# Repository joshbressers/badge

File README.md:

This code is no longer maintained, everything got too complicated. You should go to the new home of this project
https://github.com/OpenBadgeProject

# Open Badge Project

This is the Open Badge Project. The idea behind this is to have a very low cost, low power electronic badge. These could be built just for fun, or if you're throwing a conference, feel free to use the PCB as the badge, maybe build some, maybe let the folks at the conference build them.

Electronic badges have gotten pretty hip, but they seem to suffer from two primary problems.
1) They are very expensive
1) They need a lot of batteries

The goal of the Open Badge Project was to build a badge that costs $5 or less and can run for a day or more on one 2032 battery.

The badge as it stands right now will only cost $5 if you build A LOT (1000 or more). The cost is closer to $6 or $7 for smaller batches at the moment, but that's still pretty reasonable.

### Types
There are two versions of the badge. One is a through hole badge that's very easy to solder. It was designed with human fabricators in mind. The kicad files in the main branch are for the through hole model.

There is also a surface mount version in the [surface-mount](https://github.com/joshbressers/badge/tree/surface-mount) branch. This version of the badge can be sent off to a fabricator to be mass produced.

Both badge versions use the same code.

## How does it work?
The badge itself runs on a microprocessor called an ATTINY85. It has 8K of program space, 512 bytes (yes, bytes) of memory. That microprocessor then drives 3 shift registers. One for the button input, and two for the display output. Shift registers shouldn't be used to drive LEDs, but it works, and doing it this way keeps the cost down.

The PCB can be shipped off to one of the countless PCB manufacturers that exist. There is room on the front for a logo. There is also plenty of room on the back for graphics. Instructions for swapping in your own logo can be found below.

The PCB was designed using KiCad, version 7.0 to be precise. Your mileage may very if you try to use other versions.

## Parts List
You can generate a bill of materials from KiCad, but for the sake of simplicity here is a list of all the parts.

- 1 [ATTINY85](https://www.digikey.com/en/products/detail/microchip-technology/ATTINY85-20PU/735469)
- 1 PCB (you have to get this made, you can't buy them)
- 2 [CD74HC595E](https://www.digikey.com/en/products/detail/texas-instruments/CD74HC595E/1507396) shift registers
- 1 [CD4021BE](https://www.digikey.com/en/products/detail/texas-instruments/CD4021BE/67261) shift register
- 1 [2032 battery holder](https://www.digikey.com/en/products/detail/adam-tech/BH-25C-1/13537703)
- 8 [100 Ohm resistors](https://www.digikey.com/en/products/detail/stackpole-electronics-inc/CF14JT100R/1741261)
- 8 [100K Ohm resistors](https://www.digikey.com/en/products/detail/stackpole-electronics-inc/CF14JT10K0/1741265)
- 6 [Buttons](https://www.amazon.com/gp/product/B07VSNN9S2/ref=ppx_yo_dt_b_asin_title_o00_s00?ie=UTF8&th=1)
- 1 [8x8 LED Display](https://www.aliexpress.us/item/3256805713726832.html?spm=a2g0o.order_list.order_list_main.11.64611802KkD7xH&gatewayAdapt=glo2usa)

There may be better places to purchase these things than these links. Please submit a PR if you find something better.

## How to change the logo
KiCad has a tool called "Image Converter". This application lets you turn an image into a footprint that can be added to the PCB layout.

When you run the tool, there is a button on the left called "Load Source Image". If you have a black and white image to start with that's the best. You can use any image but things get weird.

Once you load an image you will need to watch the size. The "Output Size" field is what matters here. It will take a few tries to get it right. There's about 3 inches by 1.7 inches of space to work with on the front.

Use the "Front Solder Mask" layer. Make sure you use Footprint for the output layer.

Click Export to file. Save the file in the badge-footprints.pretty directory.

Now open the "PCB Editor" application. Make sure the "F. Silkscreen" layer is selected on the right.

You will have to click on and delete the existing logo. Now from the menu Place -> Add Footprint

If you search for "badge" in the text box you should see your logo show up in the list. Double click it, then place it where it fits. If the logo isn't sized right, go back to the Image Converter and try again.

## How to order PCBs
If you want to have PCBs made, you need to export the Gerber files from the PCB Editor. The Gerber files are what you send the PCB manufacturer.

Run the PCB Editor, then File -> Fabrication Outputs -> Gerbers

Create a new directory to hold the files (there will be more than one). For example let's call it badge_gerber. Leave the default settings alone, it should do the right thing.

Then click Plot. Then click "Generate Drill Files" and "Generate Drill File" on the window that pops up. Your directory now has the files need to create the PCB in it.

The PCB manufacturer will want that directory turned into a zip file and uploaded. You're on your own to figure that part out.

## How to program the chip

In order to program the ATTINY85 you will need a programmer. There is a lovely page that explains how to use an arduino as your [programmer](https://www.instructables.com/How-to-Program-an-Attiny85-From-an-Arduino-Uno/)

The reset pin on this chip is special. We are purposely not using that pin (so we really only have 5 IO pins now) because if you use the reset pin, you now require a high voltage programmer. Since we want people to program this thing using only an arduino, we'll keep the reset pin free.

## How to develop for the badge
See [DEVELOPING.md](DEVELOPING.md)

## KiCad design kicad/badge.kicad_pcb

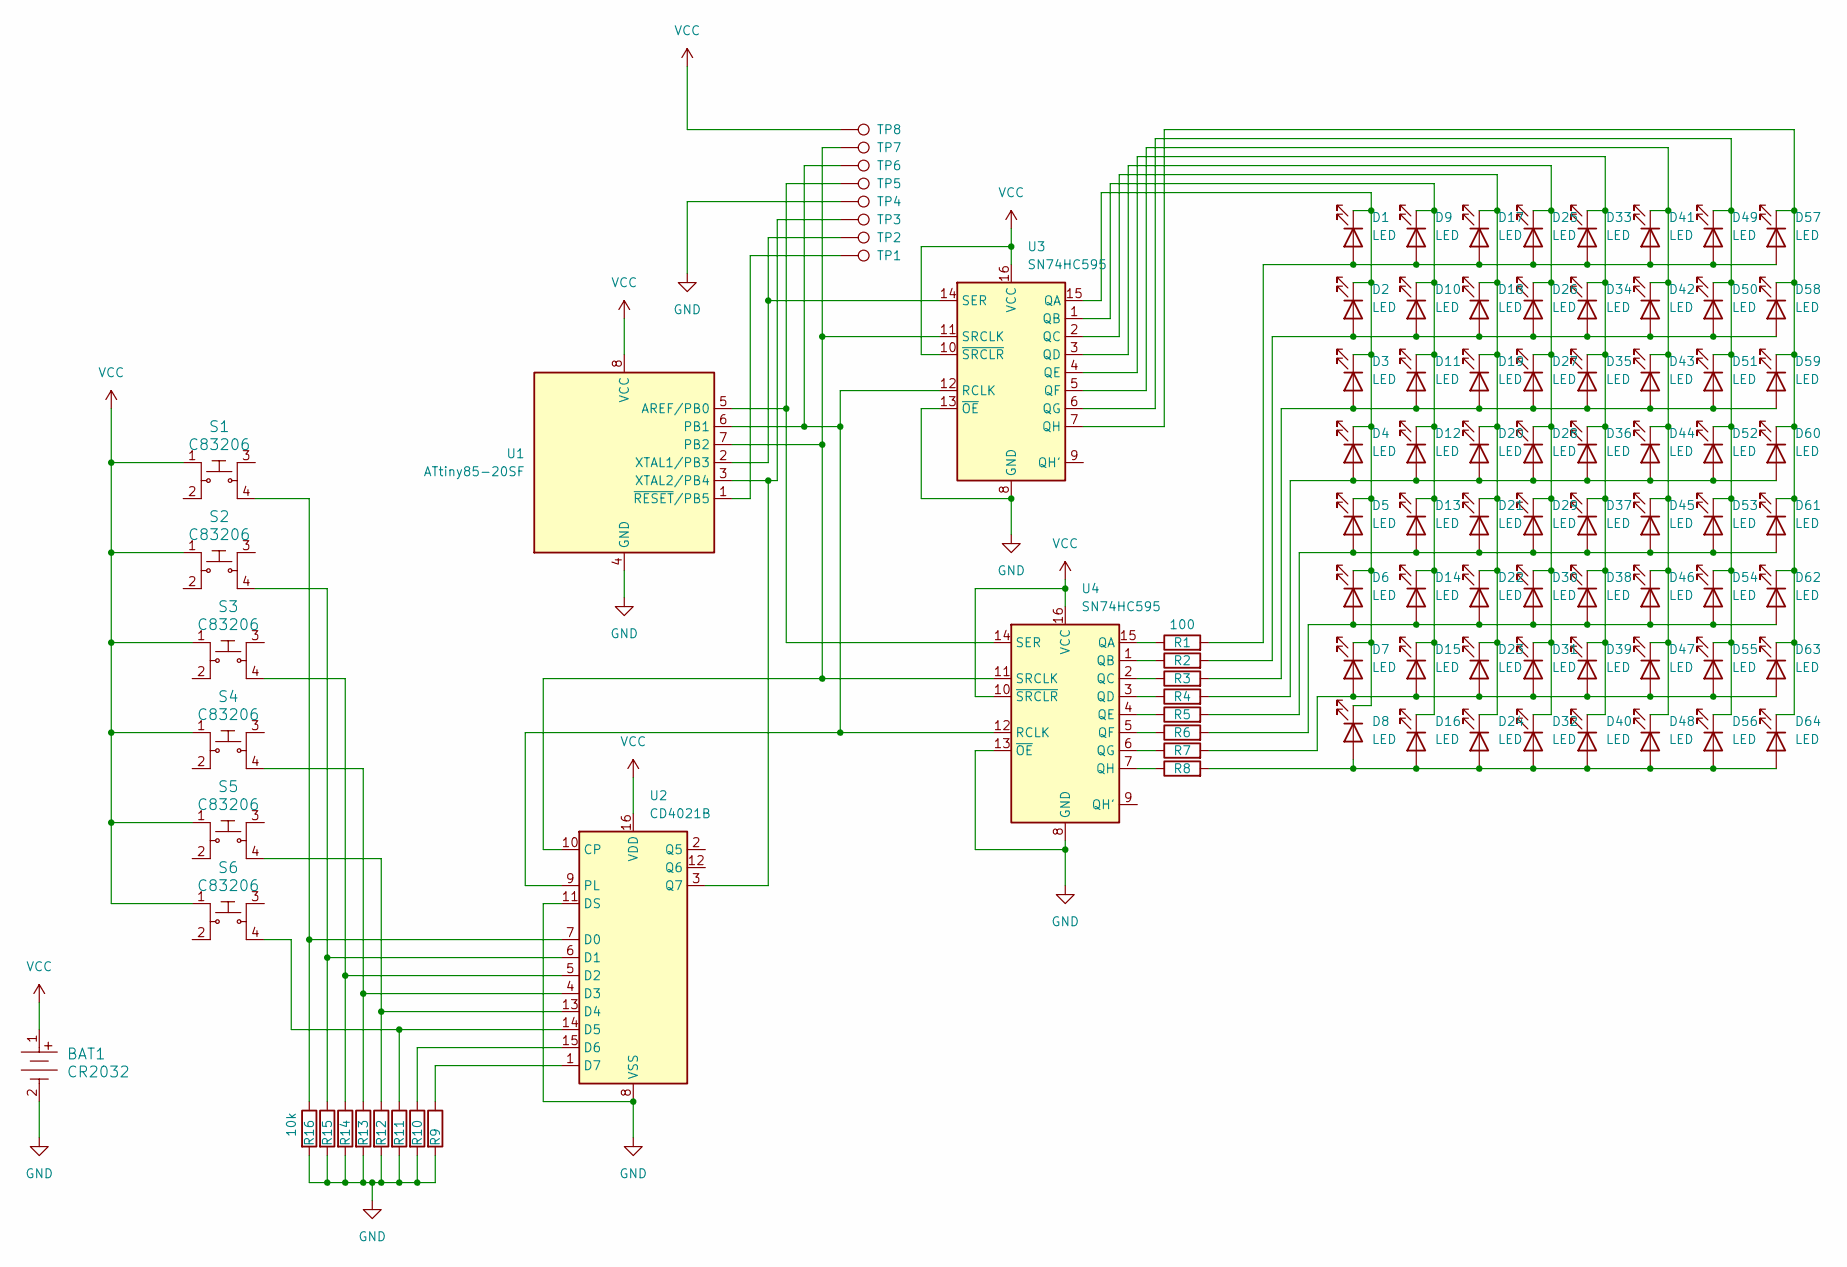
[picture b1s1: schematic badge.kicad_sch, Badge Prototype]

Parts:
BAT1: CR2032; BatteryHolder_MPD_BC2003_1x2032; MPN BS-7; JLCPCB Part # C964831
D1, D2, D3, D4, D5, D6, D7, D8, D9, D10, D11, D12, D13, D14, D15, D16, D17, D18, D19, D20, D21, D22, D23, D24, D25, D26, D27, D28, D29, D30, D31, D32, D33, D34, D35, D36, D37, D38, D39, D40, D41, D42, D43, D44, D45, D46, D47, D48, D49, D50, D51, D52, D53, D54, D55, D56, D57, D58, D59, D60, D61, D62, D63, D64: LED; LED_1206_3216Metric_Pad1.42x1.75mm_HandSolder
R1, R2, R3, R4, R5, R6, R7, R8: 100; R_0805
R9, R10, R11, R12, R13, R14, R15, R16: 10k; R_0805
S1: C83206; SW_MEC_5GSH9
S2, S3, S4, S5, S6: C83206; MPN TL3315NF160Q; Digi-Key_PN EG4621CT-ND
TP1, TP2, TP3, TP4, TP5, TP6, TP7, TP8: TestPoint; TestPoint_THTPad_D1.5mm_Drill0.7mm
U1: ATtiny85-20SF; SOIC-8_5.3x5.3mm_P1.27mm; JLCPCB Part # C615549
U2: CD4021B; SOIC-16_L9.9-W3.9-P1.27-LS6.0-BL; JLCPCB Part # C6729
U3, U4: SN74HC595; SOIC-16_L9.9-W3.9-P1.27-LS6.0-BL; JLCPCB Part # C5947

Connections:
GND: BAT1.2, R9.2, R10.2, R11.2, R12.2, R13.2, R14.2, R15.2, R16.2, TP4.1, U1.4 (GND), U2.8 (VSS), U2.11 (DS), U3.8 (GND), U3.13 (~OE), U4.8 (GND), U4.13 (~OE)
unnamed: D1.2 (A), D9.2 (A), D17.2 (A), D25.2 (A), D33.2 (A), D41.2 (A), D49.2 (A), D57.2 (A), R1.2
unnamed: D1.1 (K), D2.1 (K), D3.1 (K), D4.1 (K), D5.1 (K), D6.1 (K), D7.1 (K), D8.1 (K), U3.15 (QA)
unnamed: D2.2 (A), D10.2 (A), D18.2 (A), D26.2 (A), D34.2 (A), D42.2 (A), D50.2 (A), D58.2 (A), R2.2
unnamed: D9.1 (K), D10.1 (K), D11.1 (K), D12.1 (K), D13.1 (K), D14.1 (K), D15.1 (K), D16.1 (K), U3.1 (QB)
unnamed: D3.2 (A), D11.2 (A), D19.2 (A), D27.2 (A), D35.2 (A), D43.2 (A), D51.2 (A), D59.2 (A), R3.2
unnamed: D4.2 (A), D12.2 (A), D20.2 (A), D28.2 (A), D36.2 (A), D44.2 (A), D52.2 (A), D60.2 (A), R4.2
unnamed: D5.2 (A), D13.2 (A), D21.2 (A), D29.2 (A), D37.2 (A), D45.2 (A), D53.2 (A), D61.2 (A), R5.2
unnamed: D6.2 (A), D14.2 (A), D22.2 (A), D30.2 (A), D38.2 (A), D46.2 (A), D54.2 (A), D62.2 (A), R6.2
unnamed: D7.2 (A), D15.2 (A), D23.2 (A), D31.2 (A), D39.2 (A), D47.2 (A), D55.2 (A), D63.2 (A), R7.2
unnamed: D8.2 (A), D16.2 (A), D24.2 (A), D32.2 (A), D40.2 (A), D48.2 (A), D56.2 (A), D64.2 (A), R8.2
unnamed: D17.1 (K), D18.1 (K), D19.1 (K), D20.1 (K), D21.1 (K), D22.1 (K), D23.1 (K), D24.1 (K), U3.2 (QC)
unnamed: D25.1 (K), D26.1 (K), D27.1 (K), D28.1 (K), D29.1 (K), D30.1 (K), D31.1 (K), D32.1 (K), U3.3 (QD)
unnamed: D33.1 (K), D34.1 (K), D35.1 (K), D36.1 (K), D37.1 (K), D38.1 (K), D39.1 (K), D40.1 (K), U3.4 (QE)
unnamed: D41.1 (K), D42.1 (K), D43.1 (K), D44.1 (K), D45.1 (K), D46.1 (K), D47.1 (K), D48.1 (K), U3.5 (QF)
unnamed: D49.1 (K), D50.1 (K), D51.1 (K), D52.1 (K), D53.1 (K), D54.1 (K), D55.1 (K), D56.1 (K), U3.6 (QG)
unnamed: D57.1 (K), D58.1 (K), D59.1 (K), D60.1 (K), D61.1 (K), D62.1 (K), D63.1 (K), D64.1 (K), U3.7 (QH)
unnamed: TP5.1, U1.5 (AREF/PB0), U4.14 (SER)
unnamed: TP6.1, U1.6 (PB1), U2.9 (PL), U3.12 (RCLK), U4.12 (RCLK)
unnamed: TP7.1, U1.7 (PB2), U2.10 (CP), U3.11 (SRCLK), U4.11 (SRCLK)
unnamed: TP2.1, U1.2 (XTAL1/PB3), U3.14 (SER)
unnamed: TP3.1, U1.3 (XTAL2/PB4), U2.3 (Q7)
unnamed: TP1.1, U1.1 (~RESET/PB5)
unnamed: R16.1, S1.4, U2.7 (D0)
unnamed: R15.1, S2.4, U2.6 (D1)
unnamed: R14.1, S3.4, U2.5 (D2)
unnamed: R13.1, S4.4, U2.4 (D3)
unnamed: R12.1, S5.4, U2.13 (D4)
unnamed: R11.1, S6.4, U2.14 (D5)
unnamed: R10.1, U2.15 (D6)
unnamed: R9.1, U2.1 (D7)
unnamed: R1.1, U4.15 (QA)
unnamed: R2.1, U4.1 (QB)
unnamed: R3.1, U4.2 (QC)
unnamed: R4.1, U4.3 (QD)
unnamed: R5.1, U4.4 (QE)
unnamed: R6.1, U4.5 (QF)
unnamed: R7.1, U4.6 (QG)
unnamed: R8.1, U4.7 (QH)
VCC: BAT1.1, S1.1, S2.1, S3.1, S4.1, S5.1, S6.1, TP8.1, U1.8 (VCC), U2.16 (VDD), U3.10 (~SRCLR), U3.16 (VCC), U4.10 (~SRCLR), U4.16 (VCC)

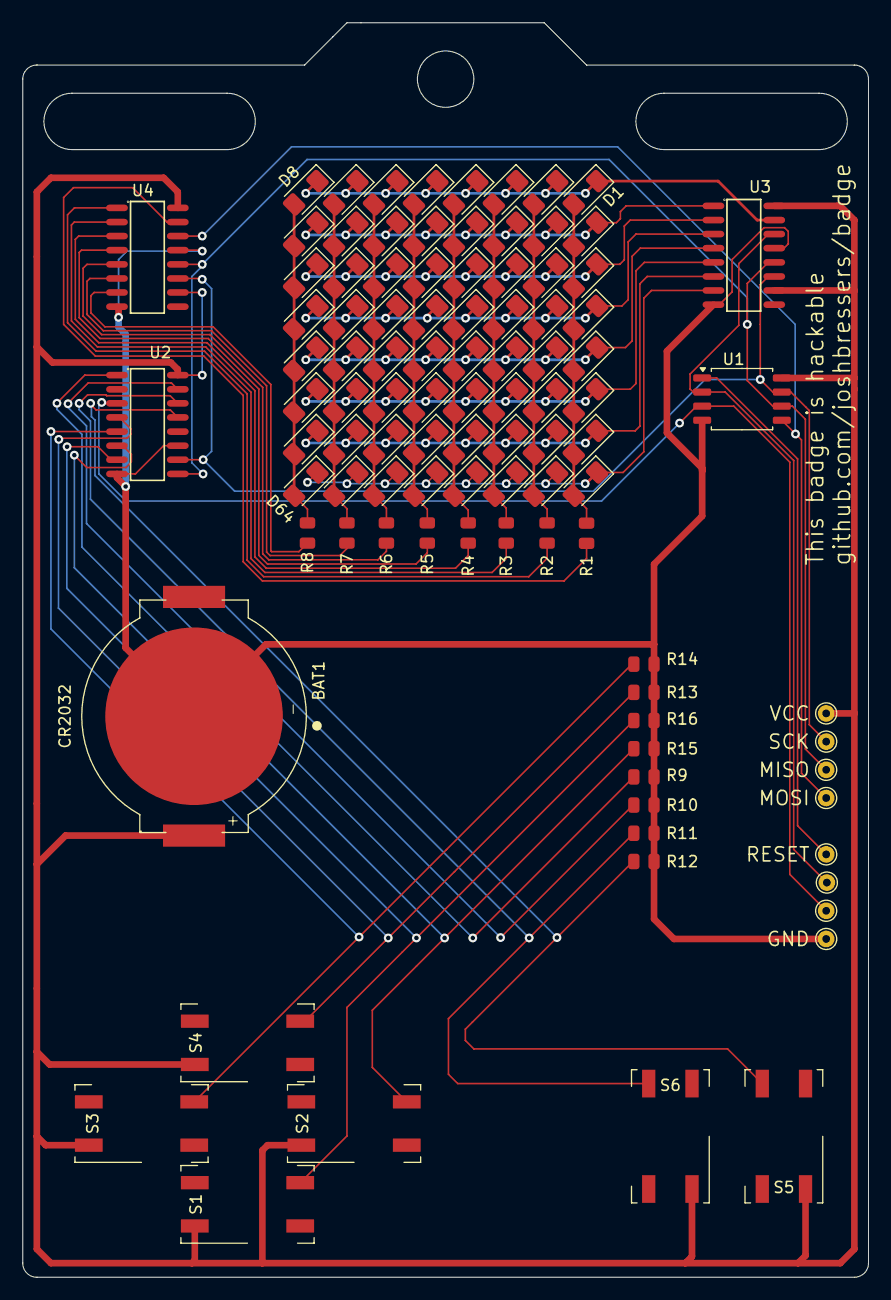
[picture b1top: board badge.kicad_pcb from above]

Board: 2 copper layers, 76.2 x 113.0 mm, 99 parts (0 on the bottom side), 40 nets.

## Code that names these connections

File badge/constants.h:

#ifndef CONSTANTS_H
#define CONSTANTS_H

#include <avr/io.h>
#include "font.h"

// Things you might want to change are all located here

// Games to enable
//#define DotGame
//#define PongGame
//#define SpaceGame
//#define RainGame
//#define BlockGame
//#define CustomMessage
//#define EnableTests

// Comment this out if you don't want a secret code
//#define SecretCode

// This is the default message that scrolls across the badge by default
const char defaultMessage[] PROGMEM = "Default Badge Message ";
const char codez[] PROGMEM = "sekrit codez!!!  ";

// The speed at which the message scrolls. Bigger numbers scroll slower
#define messageDelay 30

// How many ticks should we wait until we return to home screen
// Bigger numbers wait longer
#define HOME_TIMEOUT 3000


// Below here are things you probably shouldn't change


// Constants

// Hardware related constants

// Shift register pins
#define latchPin PB1
#define clockPin PB2

////Pin connected to DS of 74HC595
#define dataPin1 PB0 // SR 1
#define dataPin2 PB3 // SR 2
#define buttonPin PB4 // Button Input

// Frame buffer variables
byte frameBuffer[] = {0,0,0,0,0,0,0,0};

// Message display constants
const char* message;
unsigned int messageLen = 0;

const char scoreMessage[] PROGMEM = "Score ";


// Constants used when writing the message to the framebuffer
unsigned int messageCount = 0;
unsigned int lastButton = 0;

// Tick constants
// The millis() on this chip isn't very reliable, so let's just count up a tick
// on every loop
unsigned int currentTick = 0;

// State booleans
bool donePrinting = false;

// TICK can be used for delay loops. Pass it in a value to return true
// after a certain amount of time has passed.
#define TICK(the_tick) (!(currentTick % the_tick))

// This has to be run by every function. A timeout of zero can be passed in
// to not ever timeout. If no timeout is used it's up to the function
// to return
#define LOOP(loop_define_timeout) {\
  runTick();\
  if (loop_define_timeout && (lastButton > loop_define_timeout)) {\
    return;\
  }\
}

// The Arduino random() code uses up 500 bytes, we'll use our own
#define RANDOM(rand_ceiling) (random32() % rand_ceiling)

// Button Constants
#define BTN_A 0x10
#define BTN_B 0x20
#define BTN_LEFT 0x04
#define BTN_RIGHT 0x02
#define BTN_UP 0x08
#define BTN_DOWN 0x01

uint8_t CUR_BUTTON = 0x00;
uint8_t OLD_BUTTON = 0x00;

// Button functionality

// This will return true if a button is pressed for the first time
// A held down button will return false
#define NEW_BUTTON(the_btn) ((CUR_BUTTON & the_btn) && !(OLD_BUTTON & the_btn))

// Return true if the button is pressed
#define PUSH_BUTTON(the_btn) (CUR_BUTTON & the_btn)

// Define our functions here
void setMessage(unsigned char *newMessage, bool progMem);
void printMessage(unsigned char *newMessage, bool progmemMessage);
void printScore(unsigned int score);
void shiftRegisters();
void showMessage();
void clearFrameBuffer();
void moveDot();
void showMenu();
void screenTest();
void buttonTest();
void runTick();
void pongGame();
void spaceGame();
void showRain();
void customMessage();
uint32_t random32();
void teh_code();
void badgeBlock();
void getString(unsigned char *theString);



// Main Menu things

// Menu static text
const char menu0[] PROGMEM = "Menu ";
const char menu1[] PROGMEM = "Test Buttons ";
const char menu2[] PROGMEM = "Dot ";
const char menu3[] PROGMEM = "Test Screen ";
const char menu4[] PROGMEM = "Pong ";
const char menu5[] PROGMEM = "Space ";
const char menu6[] PROGMEM = "Rain ";
const char menu7[] PROGMEM = "Custom Message ";
const char menu8[] PROGMEM = "Badgetris ";

typedef struct badgeStruct {
  const char *programName;
  void (*badgeFunction)(void);
};

badgeStruct mainMenu[] = {
  {
    menu0,
    NULL
  },
#ifdef CustomMessage
  {
    menu7,
    (*customMessage)
  },
#endif
#ifdef BlockGame
  {
    menu8,
    (*badgeBlock)
  },
#endif
#ifdef RainGame
  {
    menu6,
    (*showRain)
  },
#endif
#ifdef DotGame
  {
    menu2,
    (*moveDot)
  },
#endif
#ifdef PongGame
  {
    menu4,
    (*pongGame)
  },
#endif
#ifdef SpaceGame
  {
    menu5,
    (*spaceGame)
  },
#endif
#ifdef EnableTests
  {
    menu1,
    (*buttonTest)
  },

  {
    menu3,
    (*screenTest)
  }
#endif

};

uint8_t mainMenuLen = sizeof(mainMenu) / sizeof(mainMenu[0]);
void showMenu(badgeStruct *thePrograms, uint8_t menuMax, uint16_t menuTimeout);

#endif

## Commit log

2023-08-28 Add initial files
2023-08-29 Update RADME
2023-08-29 Rename main program file
2023-08-29 Move things around to make the Arduino IDE happy
2023-08-29 Add comments
2023-08-29 Make the screen display any string
2023-08-29 Break functions into their own files
2023-08-30 Fix scrolling
2023-09-06 Update code with a timeout
2023-09-06 Use PROGMEM for strings
2023-09-06 Add a simple menu
2023-09-06 Add a lot of comments
2023-09-08 Add a move dot program
2023-09-08 Use uint8_t instead of float
2023-09-08 Use an array of strings for messages
2023-09-09 Rework the control flow
2023-09-09 Fix the button reading
2023-09-09 Add pong game
2023-09-10 Add score to pong
2023-09-10 Add space game
2023-09-10 Fix the strings and fonts
2023-09-10 Make the pong ball move better
2023-09-11 Don't use the random function
2023-09-11 Fix the screen test
2023-09-15 Add the kicad files
2023-09-16 Update badge with latest version
2023-09-16 Update the readme with instructions
2023-09-16 Add more docs
2023-09-16 Fix some typos
2023-09-22 Update badge PCB
2023-09-23 Use correct buttons
2023-09-23 Use an interrupt to drive the display
2023-09-23 Clear the last column
2023-09-23 Run the system at 60FPS
2023-09-25 Speed up the shift register handling
2023-09-28 Add changes to badge to match reality
2023-09-28 Fix the revision numbers
2023-09-28 Add a delay
2023-10-09 Add a badge GIF image
2023-10-09 Add a note about interrupts
2023-10-09 Add PCB image
2023-11-14 Add initial badgetris game
2023-11-14 Add the tetris game for real
2023-11-21 Fix badgetris
2025-02-22 Add code for surface mount badge
2025-06-09 Update message
2025-06-20 Add surface mount parts
2025-09-13 Update surface mount badge
2025-09-13 Update badge
2025-09-18 Show menu correctly
2025-09-20 Use the registers instead of digital read/write
2025-09-20 Update register IO
2025-09-20 Update labels
2025-09-23 Add Rain
2025-09-23 Add a rain app
2025-09-23 Clean up the code
2025-09-23 Move the rain game and rename dot
2025-09-23 Move the things you should modify
2025-09-23 Fix the space game
2025-09-23 Add rain game
2025-09-24 Use integers instead of float for space
2025-09-24 Make the menu a reusable function
2025-09-25 Add a custom message
2025-09-25 Fix menu timing
2025-09-25 Fix some defaults
2025-09-28 Add badgetris
2025-09-28 Fix a typo
2025-09-28 Simplify the secret code
2025-09-28 Remove the gap filler from the font
2025-09-28 Fix the test for end of string
2025-09-28 Optimize things
2025-09-29 Clean up the set message function
2025-09-29 Update the secret code code
2025-09-30 Change defaults to work at 1MHz
2025-10-02 Add a simple python programmer
2025-10-05 Update the auto progammer
2025-10-05 Make the light blink
2025-10-06 Make the secret code optional
2025-10-06 Allow a getString function
2025-10-06 Don't allow a rain speed of zero
2025-10-07 Update the text files
